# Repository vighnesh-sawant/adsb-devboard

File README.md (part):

# adsb-devboard
A devboard with an fpga  and an ADS-B reciever

# Why
When I was younger, I always wanted to tinker with radio stuff. When I learned airplanes broadcast  
all of their info on rf just like that, I tried naievly to process that using my phone thinking it had a rf reciever so it probably can.  
As it turns out it can't/ or is locked down so it can't.
So on learning about blueprint, I made by childhood dream come true!

# How
Get the pcb and a antenna(should be able to do for 1090Mhz),wire it to the correct gpio ports(more info soon)  
keep it in an open area, then flashing my firmware (not complete yet) should get you data about a good amount of flights in the vicinity    
(according to my research 50km ish)(more details once i try this out, I have done research but yk Murphy's law once I try out I'll have solid instructions!)

# Pics

# Bom
| JLCPCB BOM Tool - BOM Matching                                                      |                   |                             |                                          |               |                    |                        |                                                                                                                                                           |                 |                                                                                                                                                                                   |                                              |                                                                                                                                                                                                                              |                   |                                                                          |          |     |           |                 |
| ----------------------------------------------------------------------------------- | ----------------- | --------------------------- | ---------------------------------------- | ------------- | ------------------ | ---------------------- | --------------------------------------------------------------------------------------------------------------------------------------------------------- | --------------- | --------------------------------------------------------------------------------------------------------------------------------------------------------------------------------- | -------------------------------------------- | ---------------------------------------------------------------------------------------------------------------------------------------------------------------------------------------------------------------------------- | ----------------- | ------------------------------------------------------------------------ | -------- | --- | --------- | --------------- |
| BOM name：rev3_bom-JLCPCB Assembly Order.xlsx                                        |                   |                             | Download Time：2026-03-01 03:22:45        |               |                    |                        | * Our matching results are updated in real-time, but stock and prices may change. 
If it's been over 24 hours, please re-match before placing your order. |                 |                                                                                                                                                                                   |                                              |                                                                                                                                                                                                                              |                   |                                                                          |          |     |           |                 |
| PCB Assembled Qty：5                                                                 |                   |                             | Est. Total Price：59.8411                 |               |                    |                        |                                                                                                                                                           |                 |                                                                                                                                                                                   |                                              |                                                                                                                                                                                                                              |                   |                                                                          |          |     |           |                 |
| Your BOM                                                                            |                   |                             |                                          |               | Matched Parts      |                        |                                                                                                                                                           |                 |                                                                                                                                                                                   |                                              |                                                                                                                                                                                                                              | Order Information |                                                                          |          |     |           |                 |
| Top Designator                                                                      | Bottom Designator | Comment                     | Footprint                                | JLCPCB Part # | Matches            | Part #                 | Manufacturer                                                                                                                                              | Footprint       | Description                                                                                                                                                                       | Category                                     | Warning                                                                                                                                                                                                                      | JLCPCB Part #     | Product link                                                             | Lib Type | Qty | Source    | Total Price ($) |
| C1,C2                                                                               |                   | 33p                         | 0402                                     |               | Unconfirmed        | 0402CG330J500NT        | FH (Guangdong Fenghua Advanced Tech)                                                                                                                      | 0402            | 33pF 50V C0G ±5% 0402 Multilayer Ceramic Capacitors MLCC - SMD/SMT ROHS                                                                                                           | Multilayer Ceramic Capacitors MLCC - SMD/SMT | 1.The comment (0402CG330J500NT) of this part does not match the one (33p) provided in your BOM. Please confirm;                                                                                                              | C1562             | https://jlcpcb.com/partdetail/1914-0402CG330J500NT/C1562                 | Basic    | 4   | 4 JLCPCB  | 0.0048          |
| C10,C11,C12,C13,C14,C15,C17,C18,C19,C21,C33,C35,C37,C41,C43,C45,C47,C48,C6,C7,C8,C9 |                   | 100n                        | 0402                                     |               | Unconfirmed        | CL05B104KO5NNNC        | Samsung Electro-Mechanics                                                                                                                                 | 0402            | 100nF 16V X7R ±10% 0402 Multilayer Ceramic Capacitors MLCC - SMD/SMT ROHS                                                                                                         | Multilayer Ceramic Capacitors MLCC - SMD/SMT | 1.The comment (CL05B104KO5NNNC) of this part does not match the one (100n) provided in your BOM. Please confirm;                                                                                                             | C1525             | https://jlcpcb.com/partdetail/1877-CL05B104KO5NNNC/C1525                 | Basic    | 44  | 44 JLCPCB | 0.0572          |
| C16,C23,C3,C32,C34,C36,C38,C4,C40,C42,C44,C5                                        |                   | 4.7u                        | 0402                                     |               | Unconfirmed        | CL05A475MP5NRNC        | Samsung Electro-Mechanics                                                                                                                                 | 0402            | 10V 4.7uF X5R ±20% 0402 Multilayer Ceramic Capacitors MLCC - SMD/SMT ROHS                                                                                                         | Multilayer Ceramic Capacitors MLCC - SMD/SMT | 1.The comment (CL05A475MP5NRNC) of this part does not match the one (4.7u) provided in your BOM. Please confirm;                                                                                                             | C23733            | https://jlcpcb.com/partdetail/24469-CL05A475MP5NRNC/C23733               | Basic    | 24  | 24 JLCPCB | 0.12            |
| C20,C22                                                                             |                   | 22u                         | 0603                                     |               | Unconfirmed        | CL10A226MQ8NRNC        | Samsung Electro-Mechanics                                                                                                                                 | 0603            | 22uF 6.3V X5R ±20% 0603 Multilayer Ceramic Capacitors MLCC - SMD/SMT ROHS                                                                                                         | Multilayer Ceramic Capacitors MLCC - SMD/SMT | 1.The comment (CL10A226MQ8NRNC) of this part does not match the one (22u) provided in your BOM. Please confirm;                                                                                                              | C59461            | https://jlcpcb.com/partdetail/60514-CL10A226MQ8NRNC/C59461               | Basic    | 4   | 4 JLCPCB  | 0.038           |
| C24,C25                                                                             |                   | 10u                         | 0603                                     |               | Unconfirmed        | CL10A106KP8NNNC        | Samsung Electro-Mechanics                                                                                                                                 | 0603            | 10V 10uF X5R ±10% 0603 Multilayer Ceramic Capacitors MLCC - SMD/SMT ROHS                                                                                                          | Multilayer Ceramic Capacitors MLCC - SMD/SMT | 1.The comment (CL10A106KP8NNNC) of this part does not match the one (10u) provided in your BOM. Please confirm;                                                                                                              | C19702            | https://jlcpcb.com/partdetail/20411-CL10A106KP8NNNC/C19702               | Basic    | 4   | 4 JLCPCB  | 0.0264          |
| C26,C28                                                                             |                   | 680p                        | 0603                                     |               | Unconfirmed        | 0603B681K500NT         | FH (Guangdong Fenghua Advanced Tech)                                                                                                                      | 0603            | 50V 680pF X7R ±10% 0603 Multilayer Ceramic Capacitors MLCC - SMD/SMT ROHS                                                                                                         | Multilayer Ceramic Capacitors MLCC - SMD/SMT | 1.The comment (0603B681K500NT) of this part does not match the one (680p) provided in your BOM. Please confirm;                                                                                                              | C1630             | https://jlcpcb.com/partdetail/1982-0603B681K500NT/C1630                  | Extended | 20  | 20 JLCPCB | 0.064           |
| C29,C30                                                                             |                   | 100n                        | 0603                                     |               | Unconfirmed        | CC0603KRX7R9BB104      | YAGEO                                                                                                                                                     | 0603            | 100nF 50V X7R ±10% 0603 Multilayer Ceramic Capacitors MLCC - SMD/SMT ROHS                                                                                                         | Multilayer Ceramic Capacitors MLCC - SMD/SMT | 1.The comment (CC0603KRX7R9BB104) of this part does not match the one (100n) provided in your BOM. Please confirm;                                                                                                           | C14663            | https://jlcpcb.com/partdetail/YAGEO-CC0603KRX7R9BB104/C14663             | Basic    | 4   | 4 JLCPCB  | 0.01            |
| C31                                                                                 |                   | 1000p                       | 0402                                     |               | Unconfirmed        | 0402B102K500NT         | FH (Guangdong Fenghua Advanced Tech)                                                                                                                      | 0402            | 1nF 50V X7R ±10% 0402 Multilayer Ceramic Capacitors MLCC - SMD/SMT ROHS                                                                                                           | Multilayer Ceramic Capacitors MLCC - SMD/SMT | 1.The comment (0402B102K500NT) of this part does not match the one (1000p) provided in your BOM. Please confirm;                                                                                                             | C1523             | https://jlcpcb.com/partdetail/1875-0402B102K500NT/C1523                  | Basic    | 2   | 2 JLCPCB  | 0.0024          |
| C39                                                                                 |                   | 10u                         | 0402                                     |               | Unconfirmed        | CL05A106MQ5NUNC        | Samsung Electro-Mechanics                                                                                                                                 | 0402            | 10uF 6.3V X5R ±20% 0402 Multilayer Ceramic Capacitors MLCC - SMD/SMT ROHS                                                                                                         | Multilayer Ceramic Capacitors MLCC - SMD/SMT | 1.The comment (CL05A106MQ5NUNC) of this part does not match the one (10u) provided in your BOM. Please confirm;                                                                                                              | C15525            | https://jlcpcb.com/partdetail/16204-CL05A106MQ5NUNC/C15525               | Basic    | 2   | 2 JLCPCB  | 0.0112          |
| C46                                                                                 |                   | 1500p                       | 0603                                     |               | Select by Customer | 0603B152K500NT         | FH (Guangdong Fenghua Advanced Tech)                                                                                                                      | 0603            | 1.5nF 50V X7R ±10% 0603 Multilayer Ceramic Capacitors MLCC - SMD/SMT ROHS                                                                                                         | Multilayer Ceramic Capacitors MLCC - SMD/SMT | 1.The comment (0603B152K500NT) of this part does not match the one (1500p) provided in your BOM. Please confirm;
2.Multiple lines in the BOM have been matched to the same part. Please check if the matching is correct. ;  | C1595             | https://jlcpcb.com/partdetail/1947-0603B152K500NT/C1595                  | Extended | 20  | 20 JLCPCB | 0.058           |
| C52                                                                                 |                   | 1500pf                      | 0603                                     |               | Select by Customer | 0603B152K500NT         | FH (Guangdong Fenghua Advanced Tech)                                                                                                                      | 0603            | 1.5nF 50V X7R ±10% 0603 Multilayer Ceramic Capacitors MLCC - SMD/SMT ROHS                                                                                                         | Multilayer Ceramic Capacitors MLCC - SMD/SMT | 1.The comment (0603B152K500NT) of this part does not match the one (1500pf) provided in your BOM. Please confirm;
2.Multiple lines in the BOM have been matched to the same part. Please check if the matching is correct. ; | C1595             | https://jlcpcb.com/partdetail/1947-0603B152K500NT/C1595                  | Extended | 20  | 20 JLCPCB | 0.058           |
| C49                                                                                 |                   | 2.2u                        | 0603                                     |               | Unconfirmed        | CL10A225KO8NNNC        | Samsung Electro-Mechanics                                                                                                                                 | 0603            | 16V 2.2uF X5R ±10% 0603 Multilayer Ceramic Capacitors MLCC - SMD/SMT ROHS                                                                                                         | Multilayer Ceramic Capacitors MLCC - SMD/SMT | 1.The comment (CL10A225KO8NNNC) of this part does not match the one (2.2u) provided in your BOM. Please confirm;                                                                                                             | C23630            | https://jlcpcb.com/partdetail/24366-CL10A225KO8NNNC/C23630               | Basic    | 2   | 2 JLCPCB  | 0.0124          |
| C50                                                                                 |                   | 1000p                       | 0603                                     |               | Unconfirmed        | CL10B102KB8NNNC        | Samsung Electro-Mechanics                                                                                                                                 | 0603            | 1nF 50V X7R ±10% 0603 Multilayer Ceramic Capacitors MLCC - SMD/SMT ROHS                                                                                                           | Multilayer Ceramic Capacitors MLCC - SMD/SMT | 1.The comment (CL10B102KB8NNNC) of this part does not match the one (1000p) provided in your BOM. Please confirm;                                                                                                            | C1588             | https://jlcpcb.com/partdetail/1940-CL10B102KB8NNNC/C1588                 | Basic    | 2   | 2 JLCPCB  | 0.0066          |
| C53                                                                                 |                   | 3p                          | 0603                                     |               | Unconfirmed        | 0603CG3R0C500NT        | FH (Guangdong Fenghua Advanced Tech)                                                                                                                      | 0603            | 3pF 50V C0G 0603 Multilayer Ceramic Capacitors MLCC - SMD/SMT ROHS                                                                                                                | Multilayer Ceramic Capacitors MLCC - SMD/SMT | 1.The comment (0603CG3R0C500NT) of this part does not match the one (3p) provided in your BOM. Please confirm;                                                                                                               | C46219            | https://jlcpcb.com/partdetail/47222-0603CG3R0C500NT/C46219               | Extended | 20  | 20 JLCPCB | 0.062           |
| C54                                                                                 |                   | 200p                        | 0603                                     |               | Unconfirmed        | 0603B201K500NT         | FH (Guangdong Fenghua Advanced Tech)                                                                                                                      | 0603            | 200pF 50V X7R ±10% 0603 Multilayer Ceramic Capacitors MLCC - SMD/SMT ROHS                                                                                                         | Multilayer Ceramic Capacitors MLCC - SMD/SMT | 1.The comment (0603B201K500NT) of this part does not match the one (200p) provided in your BOM. Please confirm;                                                                                                              | C1600             | https://jlcpcb.com/partdetail/1952-0603B201K500NT/C1600                  | Extended | 20  | 20 JLCPCB | 0.088           |
| D1,D2,D3,D4,D5,D6                                                                   |                   | LED                         | 0603                                     |               | Unconfirmed        | KT-0603W               | Hubei KENTO Elec                                                                                                                                          | 0603            | 100mW 120° 2.6V~3.1V 360mcd 5mA Discrete Diode Top-mount White Yellow Lens 0603 LED Indication - Discrete ROHS                                                                    | LED Indication - Discrete                    | 1.The comment (KT-0603W) of this part does not match the one (LED) provided in your BOM. Please confirm;                                                                                                                     | C2290             | https://jlcpcb.com/partdetail/Hubei_KENTOElec-KT0603W/C2290              | Basic    | 12  | 12 JLCPCB | 0.1416          |
| FB1,FB2,FB3                                                                         |                   | FerriteBead                 | 0603                                     |               | Select by Customer | GZ1608D601TF           | Sunlord                                                                                                                                                   | 0603            | -55℃~+125℃ 1 200mA 450mΩ 600Ω@100MHz ±25% 0603 Ferrite Beads ROHS                                                                                                                 | Ferrite Beads                                |                                                                                                                                                                                                                              | C1002             | https://jlcpcb.com/partdetail/Sunlord-GZ1608D601TF/C1002                 | Basic    | 6   | 6 JLCPCB  | 0.0792          |
| J1                                                                                  |                   | USB_C_Receptacle_USB2.0_16P | USB_C_Receptacle_XKB_U262-16XN-4BVC11    |               | Select by Customer | TYPE-C 16PIN 2MD(073)  | SHOU HAN                                                                                                                                                  | SMD             | -25℃~+85℃ 1 16P 3A 5,000 times 5V Black Female Surface Mount, Right Angle Type-C SMD USB Connectors ROHS                                                                          | USB Connectors                               |                                                                                                                                                                                                                              | C2765186          | https://jlcpcb.com/partdetail/SHOUHAN-TYPE_C_16PIN_2MD_073/C2765186      | Extended | 3   | 3 JLCPCB  | 0.1953          |
| L1,L2,L3                                                                            |                   | AOTA-B201610S3R3-101-T      | IND-SMD_L2.0-W1.6_AOTA-B201610S3R3-101-T |               | Select by System   | AOTA-B201610S3R3-101-T | Abracon LLC                                                                                                                                               | 0806            | 0806 Power Inductors ROHS                                                                                                                                                         | Power Inductors                              |                                                                                                                                                                                                                              | C42411119         | https://jlcpcb.com/partdetail/AbraconLLC-AOTA_B201610S3R3_101T/C42411119 | Extended | 6   | 6 JLCPCB  | 1.7286          |
| L4,L5                                                                               |                   | HP0603-R10H-N               | IND-SMD_L1.6-W1.0                        |               | Select by System   | HP0603-R10H-N          | Chilisin Elec                                                                                                                                             | SMD,1.6x1mm     | 1.7GHz 100nH 470mA 49@150MHz 540mΩ Wire-wound chip inductor ±3% SMD,1.6x1mm Inductors (SMD) ROHS                                                                                  | Inductors (SMD)                              |                                                                                                                                                                                                                              | C2903685          | https://jlcpcb.com/partdetail/ChilisinElec-HP0603_R10HN/C2903685         | Extended | 6   | 6 JLCPCB  | 0.5478          |
| R1,R2                                                                               |                   | 5.1k                        | 0402                                     |               | Unconfirmed        | 0402WGF5101TCE         | UNI-ROYAL(Uniroyal Elec)                                                                                                                                  | 0402            | -55℃~+155℃ 5.1kΩ 50V 62.5mW Thick Film Resistor ±1% ±100ppm/℃ 0402 Chip Resistor - Surface Mount ROHS                                                                             | Chip Resistor - Surface Mount                | 1.The comment (0402WGF5101TCE) of this part does not match the one (5.1k) provided in your BOM. Please confirm;                                                                                                              | C25905            | https://jlcpcb.com/partdetail/26648-0402WGF5101TCE/C25905                | Basic    | 4   | 4 JLCPCB  | 0.0032          |
| R3,R4                                                                               |                   | 27                          | 0402                                     |               | Unconfirmed        | 0402WGF270JTCE         | UNI-ROYAL(Uniroyal Elec)                                                                                                                                  | 0402            | -55℃~+155℃ 27Ω 50V 62.5mW Thick Film Resistor ±1% ±100ppm/℃ 0402 Chip Resistor - Surface Mount ROHS                                                                               | Chip Resistor - Surface Mount                | 1.The comment (0402WGF270JTCE) of this part does not match the one (27) provided in your BOM. Please confirm;                                                                                                                | C25100            | https://jlcpcb.com/partdetail/25843-0402WGF270JTCE/C25100                | Extended | 20  | 20 JLCPCB | 0.016           |
| R6                                                                                  |                   | 33                          | 0402                                     |               | Unconfirmed        | 0402WGF330JTCE         | UNI-ROYAL(Uniroyal Elec)                                                                                                                                  | 0402            | -55℃~+155℃ 33Ω 50V 62.5mW Thick Film Resistor ±1% ±100ppm/℃ 0402 Chip Resistor - Surface Mount ROHS                                                                               | Chip Resistor - Surface Mount                | 1.The comment (0402WGF330JTCE) of this part does not match the one (33) provided in your BOM. Please confirm;                                                                                                                | C25105            | https://jlcpcb.com/partdetail/25848-0402WGF330JTCE/C25105                | Basic    | 2   | 2 JLCPCB  | 0.0016          |
| R10,R9                                                                              |                   | 51k                         | 0402                                     |               | Unconfirmed        | 0402WGF5102TCE         | UNI-ROYAL(Uniroyal Elec)                                                                                                                                  | 0402            | -55℃~+155℃ 50V 51kΩ 62.5mW Thick Film Resistor ±1% ±100ppm/℃ 0402 Chip Resistor - Surface Mount ROHS                                                                              | Chip Resistor - Surface Mount                | 1.The comment (0402WGF5102TCE) of this part does not match the one (51k) provided in your BOM. Please confirm;                                                                                                               | C25794            | https://jlcpcb.com/partdetail/26537-0402WGF5102TCE/C25794                | Basic    | 4   | 4 JLCPCB  | 0.0036          |
| R11                                                                                 |                   | 22k                         | 0402                                     |               | Unconfirmed        | 0402WGF2202TCE         | UNI-ROYAL(Uniroyal Elec)                                                                                                                                  | 0402            | -55℃~+155℃ 22kΩ 50V 62.5mW Thick Film Resistor ±1% ±100ppm/℃ 0402 Chip Resistor - Surface Mount ROHS                                                                              | Chip Resistor - Surface Mount                | 1.The comment (0402WGF2202TCE) of this part does not match the one (22k) provided in your BOM. Please confirm;                                                                                                               | C25768            | https://jlcpcb.com/partdetail/26511-0402WGF2202TCE/C25768                | Basic    | 2   | 2 JLCPCB  | 0.0016          |
| R12,R32                                                                             |                   | 100k                        | 0402                                     |               | Unconfirmed        | 0402WGF1003TCE         | UNI-ROYAL(Uniroyal Elec)                                                                                                                                  | 0402            | -55℃~+155℃ 100kΩ 50V 62.5mW Thick Film Resistor ±1% ±100ppm/℃ 0402 Chip Resistor - Surface Mount ROHS                                                                             | Chip Resistor - Surface Mount                | 1.The comment (0402WGF1003TCE) of this part does not match the one (100k) provided in your BOM. Please confirm;                                                                                                              | C25741            | https://jlcpcb.com/partdetail/26484-0402WGF1003TCE/C25741                | Basic    | 4   | 4 JLCPCB  | 0.0032          |
| R13                                                                                 |                   | 120                         | 0402                                     |               | Unconfirmed        | 0402WGF1200TCE         | UNI-ROYAL(Uniroyal Elec)                                                                                                                                  | 0402            | -55℃~+155℃ 120Ω 50V 62.5mW Thick Film Resistor ±1% ±100ppm/℃ 0402 Chip Resistor - Surface Mount ROHS                                                                              | Chip Resistor - Surface Mount                | 1.The comment (0402WGF1200TCE) of this part does not match the one (120) provided in your BOM. Please confirm;                                                                                                               | C25079            | https://jlcpcb.com/partdetail/25822-0402WGF1200TCE/C25079                | Basic    | 2   | 2 JLCPCB  | 0.0014          |
| R14,R15,R16,R17,R18,R19,R20,R21,R24,R27,R28                                         |                   | 100                         | 0402                                     |               | Unconfirmed        | 0402WGF1000TCE         | UNI-ROYAL(Uniroyal Elec)                                                                                                                                  | 0402            | -55℃~+155℃ 100Ω 50V 62.5mW Thick Film Resistor ±1% ±100ppm/℃ 0402 Chip Resistor - Surface Mount ROHS                                                                              | Chip Resistor - Surface Mount                | 1.The comment (0402WGF1000TCE) of this part does not match the one (100) provided in your BOM. Please confirm;                                                                                                               | C25076            | https://jlcpcb.com/partdetail/25819-0402WGF1000TCE/C25076                | Basic    | 22  | 22 JLCPCB | 0.0154          |
| R22,R30,R5,R7                                                                       |                   | 1K                          | 0402                                     |               | Unconfirmed        | 0402WGF1001TCE         | UNI-ROYAL(Uniroyal Elec)                                                                                                                                  | 0402            | -55℃~+155℃ 1kΩ 50V 62.5mW Thick Film Resistor ±1% ±100ppm/℃ 0402 Chip Resistor - Surface Mount ROHS                                                                               | Chip Resistor - Surface Mount                | 1.The comment (0402WGF1001TCE) of this part does not match the one (1K) provided in your BOM. Please confirm;                                                                                                                | C11702            | https://jlcpcb.com/partdetail/12256-0402WGF1001TCE/C11702                | Basic    | 8   | 8 JLCPCB  | 0.0056          |
| R25,R31,R8                                                                          |                   | 10K                         | 0402                                     |               | Unconfirmed        | 0402WGF1002TCE         | UNI-ROYAL(Uniroyal Elec)                                                                                                                                  | 0402            | -55℃~+155℃ 10kΩ 50V 62.5mW Thick Film Resistor ±1% ±100ppm/℃ 0402 Chip Resistor - Surface Mount ROHS                                                                              | Chip Resistor - Surface Mount                | 1.The comment (0402WGF1002TCE) of this part does not match the one (10K) provided in your BOM. Please confirm;                                                                                                               | C25744            | https://jlcpcb.com/partdetail/26487-0402WGF1002TCE/C25744                | Basic    | 6   | 6 JLCPCB  | 0.0048          |
| R26                                                                                 |                   | 2.2K                        | 0402                                     |               | Unconfirmed        | 0402WGF2201TCE         | UNI-ROYAL(Uniroyal Elec)                                                                                                                                  | 0402            | -55℃~+155℃ 2.2kΩ 50V 62.5mW Thick Film Resistor ±1% ±100ppm/℃ 0402 Chip Resistor - Surface Mount ROHS                                                                             | Chip Resistor - Surface Mount                | 1.The comment (0402WGF2201TCE) of this part does not match the one (2.2K) provided in your BOM. Please confirm;                                                                                                              | C25879            | https://jlcpcb.com/partdetail/26622-0402WGF2201TCE/C25879                | Basic    | 2   | 2 JLCPCB  | 0.0016          |
| R29                                                                                 |                   | 53.6                        | 0402                                     |               | Unconfirmed        | 0402WGF536JTCE         | UNI-ROYAL(Uniroyal Elec)                                                                                                                                  | 0402            | -55℃~+155℃ 50V 53.6Ω 62.5mW Thick Film Resistor ±1% ±100ppm/℃ 0402 Chip Resistor - Surface Mount ROHS                                                                             | Chip Resistor - Surface Mount                | 1.The comment (0402WGF536JTCE) of this part does not match the one (53.6) provided in your BOM. Please confirm;                                                                                                              | C423156           | https://jlcpcb.com/partdetail/416106-0402WGF536JTCE/C423156              | Extended | 20  | 20 JLCPCB | 0.014           |
| SW1                                                                                 |                   | SW_Push                     | SW-SMD_L3.9-W3.0-P4.45                   |               | Select by Customer | TS-1088-AR02016        | XUNPU                                                                                                                                                     | SMD,4x3mm       | -30℃~+80℃ 1.6N 100,000 cycles 12V 2mm 3mm 4mm 50mA Black Round Button SMD(SMT) Tab SPST Surface Mount,Vertical Without Bracket SMD,4x3mm Tactile Switches ROHS                    | Tactile Switches                             |                                                                                                                                                                                                                              | C720477           | https://jlcpcb.com/partdetail/XUNPU-TS_1088AR02016/C720477               | Basic    | 2   | 2 JLCPCB  | 0.096           |
| U1                                                                                  |                   | ICE40UP5K-SG48ITR           | QFN-48-1EP_7x7mm_P0.5mm_EP5.6x5.6mm      |               | Select by Customer | ICE40UP5K-SG48I        | Lattice                                                                                                                                                   | QFN-48-EP(7x7)  | -40℃~+100℃ 1171456bit 5280 660 QFN-48-EP(7x7) Programmable Logic Device (CPLDs/FPGAs) ROHS                                                                                        | Programmable Logic Device (CPLDs/FPGAs)      |                                                                                                                                                                                                                              | C2678152          | https://jlcpcb.com/partdetail/Lattice-ICE40UP5KSG48I/C2678152            | Extended | 2   | 2 JLCPCB  | 13.5164         |
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
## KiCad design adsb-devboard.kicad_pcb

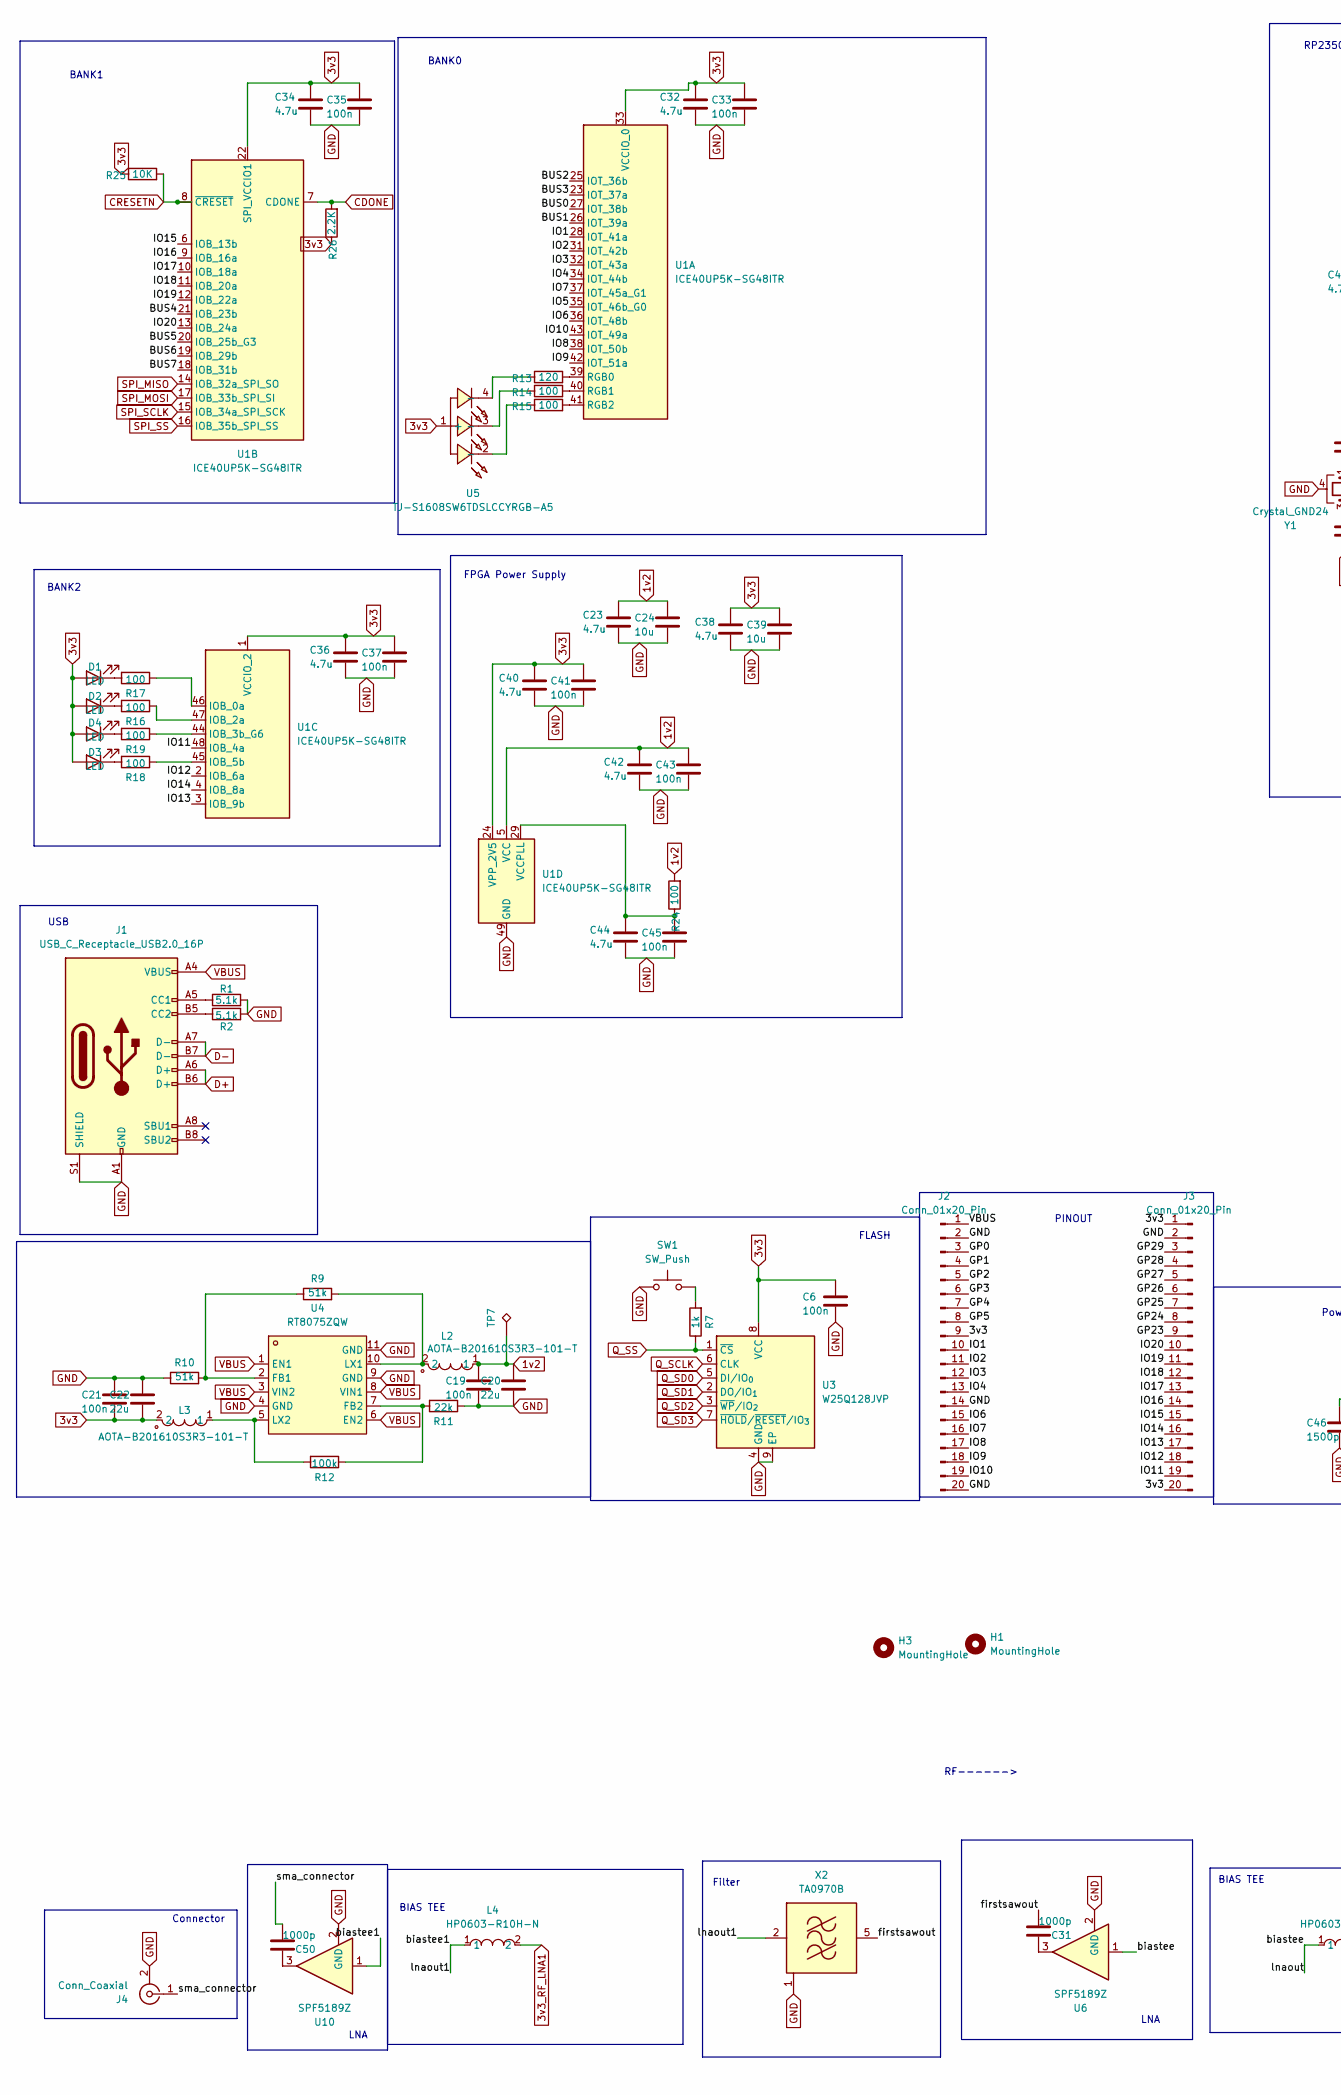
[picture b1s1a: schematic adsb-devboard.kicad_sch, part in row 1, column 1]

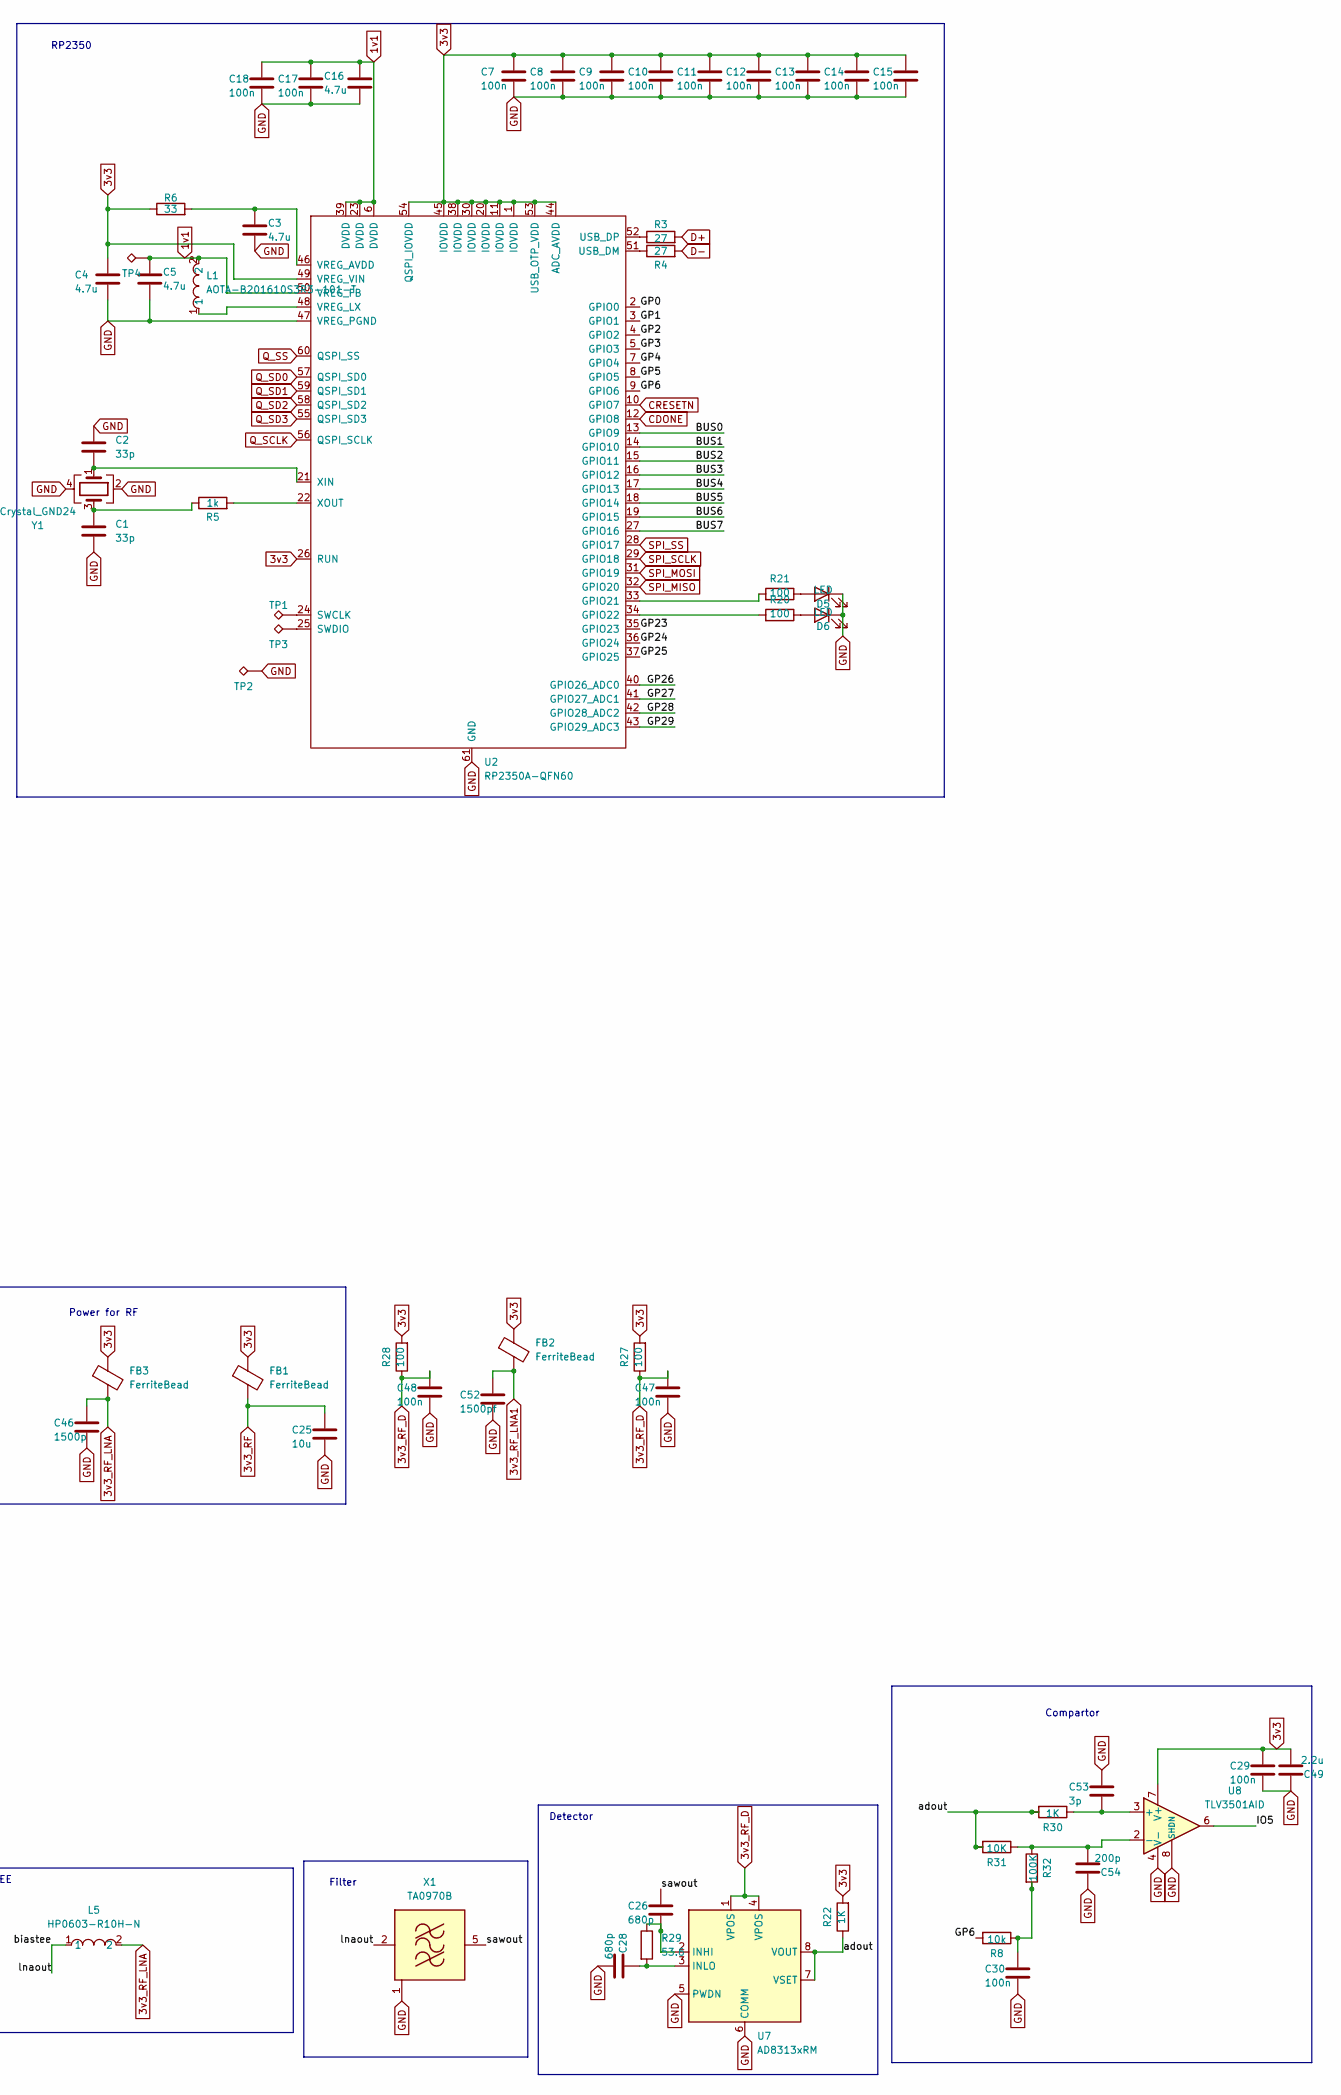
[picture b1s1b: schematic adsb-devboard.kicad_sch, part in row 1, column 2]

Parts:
C1, C2: 33p; C_0402_1005Metric
C3, C4, C5, C16, C23, C32, C34, C36, C38, C40, C42, C44: 4.7u; C_0402_1005Metric
C6, C7, C8, C9, C10, C11, C12, C13, C14, C15, C17, C18, C19, C21, C33, C35, C37, C41, C43, C45, C47, C48: 100n; C_0402_1005Metric
C20, C22: 22u; C_0603_1608Metric
C24, C25: 10u; C_0603_1608Metric
C26, C28: 680p; C_0603_1608Metric
C29, C30: 100n; C_0603_1608Metric
C31: 1000p; C_0402_1005Metric
C39: 10u; C_0402_1005Metric
C46: 1500p; C_0603_1608Metric
C49: 2.2u; C_0603_1608Metric
C50: 1000p; C_0603_1608Metric
C52: 1500pf; C_0603_1608Metric
C53: 3p; C_0603_1608Metric
C54: 200p; C_0603_1608Metric
D1, D2, D3, D4, D5, D6: LED; LED_0603_1608Metric
FB1, FB2, FB3: FerriteBead; L_0603_1608Metric
H1, H3: MountingHole; MountingHole_2.7mm_M2.5
J1: USB_C_Receptacle_USB2.0_16P; USB_C_Receptacle_XKB_U262-16XN-4BVC11
J2, J3: Conn_01x20_Pin; PinHeader_1x20_P2.54mm_Vertical
J4: Conn_Coaxial; SMA_BAT_Wireless_BWSMA-KWE-Z001
L1, L2, L3: AOTA-B201610S3R3-101-T; IND-SMD_L2.0-W1.6_AOTA-B201610S3R3-101-T; LCSC Part C42411119
L4, L5: HP0603-R10H-N; IND-SMD_L1.6-W1.0; LCSC Part C2903685
R1, R2: 5.1k; R_0402_1005Metric
R3, R4: 27; R_0402_1005Metric
R5, R7: 1k; R_0402_1005Metric
R6: 33; R_0402_1005Metric
R8: 10k; R_0402_1005Metric
R9, R10: 51k; R_0402_1005Metric
R11: 22k; R_0402_1005Metric
R12: 100k; R_0402_1005Metric
R13: 120; R_0402_1005Metric
R14, R15, R16, R17, R18, R19, R20, R21, R24, R27, R28: 100; R_0402_1005Metric
R22, R30: 1K; R_0402_1005Metric
R25, R31: 10K; R_0402_1005Metric
R26: 2.2K; R_0402_1005Metric
R29: 53.6; R_0402_1005Metric
R32: 100K; R_0402_1005Metric
SW1: SW_Push; SW-SMD_L3.9-W3.0-P4.45
TP1, TP2, TP3, TP4, TP7: TestPoint_Alt; TestPoint_Pad_D1.0mm
U1: ICE40UP5K-SG48ITR; QFN-48-1EP_7x7mm_P0.5mm_EP5.6x5.6mm
U2: RP2350A-QFN60; RP2350A_QFN-60_EP_7.75x7.75_Pitch0.4mm
U3: W25Q128JVP; WSON-8-1EP_6x5mm_P1.27mm_EP3.4x4.3mm
U4: RT8075ZQW; WDFN-10_L3.0-W3.0-P0.50-BL-EP; LCSC Part C250416
U5: TJ-S1608SW6TDSLCCYRGB-A5; LED-ARRAY-SMD_4P-L1.6-W0.8-BL-FD; LCSC Part C5356078
U6, U10: SPF5189Z; SOT-343-4_L2.0-W1.3-P1.30-LS2.1-BR
U7: AD8313xRM; MSOP-8_L3.0-W3.0-P0.65-LS4.9-BL
U8: TLV3501AID; SOP-8_L4.9-W3.9-P1.27-LS6.0-BL
X1, X2: TA0970B; FILTER-SMD_6P-L3.8-W3.8-P1.27-TL-3
Y1: Crystal_GND24; Crystal_SMD_3225-4Pin_3.2x2.5mm

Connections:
1v1: C5.1, C16.1, C17.1, C18.1, L1.2, TP4.1, U2.6 (DVDD), U2.23 (DVDD), U2.39 (DVDD), U2.50 (VREG_FB)
1v2: C19.1, C20.1, C23.1, C24.1, C42.1, C43.1, L2.1, R24.2, TP7.1, U1.5 (VCC), U1.30 (VCC)
3v3: C4.1, C6.1, C7.1, C8.1, C9.1, C10.1, C11.1, C12.1, C13.1, C14.1, C15.1, C21.2, C22.2, C29.1, C32.1, C33.1, C34.1, C35.1, C36.1, C37.1, C38.1, C39.1, C40.1, C41.1, C49.2, D1.2 (A), D2.2 (A), D3.2 (A), D4.2 (A), FB1.1, FB2.1, FB3.1, J2.9, J3.1, J3.20, L3.2, R6.1, R22.2, R25.1, R26.1, R27.2, R28.2, U1.1 (VCCIO_2), U1.22 (SPI_VCCIO1), U1.24 (VPP_2V5), U1.33 (VCCIO_0), U2.1 (IOVDD), U2.11 (IOVDD), U2.20 (IOVDD), U2.26 (RUN), U2.30 (IOVDD), U2.38 (IOVDD), U2.44 (ADC_AVDD), U2.45 (IOVDD), U2.49 (VREG_VIN), U2.53 (USB_OTP_VDD), U2.54 (QSPI_IOVDD), U3.8 (VCC), U5.1 (+), U8.7 (V+)
3v3_RF: C25.1, FB1.2
3v3_RF_D: C47.1, C48.1, R27.1, R28.1, U7.1 (VPOS), U7.4 (VPOS)
3v3_RF_LNA: C46.1, FB3.2, L5.2
3v3_RF_LNA1: C52.1, FB2.2, L4.2
/BUS0: U1.27 (IOT_38b), U2.13 (GPIO9)
/BUS1: U1.26 (IOT_39a), U2.14 (GPIO10)
/BUS2: U1.25 (IOT_36b), U2.15 (GPIO11)
/BUS3: U1.23 (IOT_37a), U2.16 (GPIO12)
/BUS4: U1.21 (IOB_23b), U2.17 (GPIO13)
/BUS5: U1.20 (IOB_25b_G3), U2.18 (GPIO14)
/BUS6: U1.19 (IOB_29b), U2.19 (GPIO15)
/BUS7: U1.18 (IOB_31b), U2.27 (GPIO16)
/GP0: J2.3, U2.2 (GPIO0)
/GP1: J2.4, U2.3 (GPIO1)
/GP2: J2.5, U2.4 (GPIO2)
/GP3: J2.6, U2.5 (GPIO3)
/GP4: J2.7, U2.7 (GPIO4)
/GP5: J2.8, U2.8 (GPIO5)
/GP6: R8.2, U2.9 (GPIO6)
/GP23: J3.9, U2.35 (GPIO23)
/GP24: J3.8, U2.36 (GPIO24)
/GP25: J3.7, U2.37 (GPIO25)
/GP26: J3.6, U2.40 (GPIO26_ADC0)
/GP27: J3.5, U2.41 (GPIO27_ADC1)
/GP28: J3.4, U2.42 (GPIO28_ADC2)
/GP29: J3.3, U2.43 (GPIO29_ADC3)
/IO1: J2.10, U1.28 (IOT_41a)
/IO2: J2.11, U1.31 (IOT_42b)
/IO3: J2.12, U1.32 (IOT_43a)
/IO4: J2.13, U1.34 (IOT_44b)
/IO5: U1.35 (IOT_46b_G0), U8.6
/IO6: J2.15, U1.36 (IOT_48b)
/IO7: J2.16, U1.37 (IOT_45a_G1)
/IO8: J2.17, U1.38 (IOT_50b)
/IO9: J2.18, U1.42 (IOT_51a)
/IO10: J2.19, U1.43 (IOT_49a)
/IO11: J3.19, U1.48 (IOB_4a)
/IO12: J3.18, U1.2 (IOB_6a)
/IO13: J3.17, U1.3 (IOB_9b)
/IO14: J3.16, U1.4 (IOB_8a)
/IO15: J3.15, U1.6 (IOB_13b)
/IO16: J3.14, U1.9 (IOB_16a)
/IO17: J3.13, U1.10 (IOB_18a)
/IO18: J3.12, U1.11 (IOB_20a)
/IO19: J3.11, U1.12 (IOB_22a)
/IO20: J3.10, U1.13 (IOB_24a)
/adout: R22.1, R30.2, R31.2, U7.7 (VSET), U7.8 (VOUT)
/biastee: L5.1, U6.1, X1.2 (IN)
/biastee1: L4.1, U10.1, X2.2 (IN)
/firstsawout: C31.2, X2.5 (OUT)
/sawout: C26.1, X1.5 (OUT)
/sma_connector: C50.2, J4.1 (In)
CDONE: R26.2, U1.7 (CDONE), U2.12 (GPIO8)
CRESETN: R25.2, U1.8 (~CRESET), U2.10 (GPIO7)
D+: J1.A6 (D+), J1.B6 (D+), R3.2
D-: J1.A7 (D-), J1.B7 (D-), R4.2
GND: C1.2, C2.1, C3.2, C4.2, C5.2, C6.2, C7.2, C8.2, C9.2, C10.2, C11.2, C12.2, C13.2, C14.2, C15.2, C16.2, C17.2, C18.2, C19.2, C20.2, C21.1, C22.1, C23.2, C24.2, C25.2, C28.2, C29.2, C30.2, C32.2, C33.2, C34.2, C35.2, C36.2, C37.2, C38.2, C39.2, C40.2, C41.2, C42.2, C43.2, C44.2, C45.2, C46.2, C47.2, C48.2, C49.1, C52.2, C53.1, C54.1, D5.1 (K), D6.1 (K), J1.A1 (GND), J1.A12 (GND), J1.B1 (GND), J1.B12 (GND), J1.S1 (SHIELD), J2.2, J2.14, J2.20, J3.2, J4.2 (Ext), R1.2, R2.2, R10.1, R11.1, SW1.1, TP2.1, U1.49 (GND), U2.47 (VREG_PGND), U2.61 (GND), U3.4 (GND), U3.9 (EP), U4.4 (GND), U4.9 (GND), U4.11 (GND), U6.2 (GND), U7.5 (PWDN), U7.6 (COMM), U8.4 (V-), U8.8 (SHDN), U10.2 (GND), X1.1 (GND), X1.3 (GND), X1.4 (GND), X1.6 (GND), X2.1 (GND), X2.3 (GND), X2.4 (GND), X2.6 (GND), Y1.2, Y1.4
unnamed: C1.1, R5.1, Y1.3
unnamed: C30.1, R8.1, R32.2
unnamed: C31.1, U6.3
unnamed: C50.1, U10.3
unnamed: D1.1 (K), R17.2
unnamed: D2.1 (K), R16.2
unnamed: D3.1 (K), R18.2
unnamed: D4.1 (K), R19.2
unnamed: D5.2 (A), R21.1
unnamed: D6.2 (A), R20.1
unnamed: J1.A5 (CC1), R1.1
unnamed: J1.B5 (CC2), R2.1
unnamed: R7.2, SW1.2
unnamed: R13.1, U5.4 (-)
unnamed: R14.1, U5.3 (-)
unnamed: R15.1, U5.2 (-)
unnamed: R13.2, U1.39 (RGB0)
unnamed: R14.2, U1.40 (RGB1)
unnamed: R15.2, U1.41 (RGB2)
unnamed: R17.1, U1.46 (IOB_0a)
unnamed: R16.1, U1.47 (IOB_2a)
unnamed: R19.1, U1.44 (IOB_3b_G6)
unnamed: R18.1, U1.45 (IOB_5b)
unnamed: C44.1, C45.1, R24.1, U1.29 (VCCPLL)
unnamed: R21.2, U2.33 (GPIO21)
unnamed: R20.2, U2.34 (GPIO22)
unnamed: TP1.1, U2.24 (SWCLK)
unnamed: TP3.1, U2.25 (SWDIO)
unnamed: R4.1, U2.51 (USB_DM)
unnamed: R3.1, U2.52 (USB_DP)
unnamed: C3.1, R6.2, U2.46 (VREG_AVDD)
unnamed: L1.1, U2.48 (VREG_LX)
unnamed: C2.2, U2.21 (XIN), Y1.1
unnamed: R5.2, U2.22 (XOUT)
unnamed: R9.1, R10.2, U4.2 (FB1)
unnamed: R11.2, R12.1, U4.7 (FB2)
unnamed: L2.2, R9.2, U4.10 (LX1)
unnamed: L3.1, R12.2, U4.5 (LX2)
unnamed: C26.2, R29.1, U7.2 (INHI)
unnamed: C28.1, R29.2, U7.3 (INLO)
unnamed: C53.2, R30.1, U8.3 (+)
unnamed: C54.2, R31.1, R32.1, U8.2 (-)
Q_SCLK: U2.56 (QSPI_SCLK), U3.6 (CLK)
Q_SD0: U2.57 (QSPI_SD0), U3.5 (DI/IO_{0})
Q_SD1: U2.59 (QSPI_SD1), U3.2 (DO/IO_{1})
Q_SD2: U2.58 (QSPI_SD2), U3.3 (~WP/IO_{2})
Q_SD3: U2.55 (QSPI_SD3), U3.7 (~HOLD/~RESET/IO_{3})
Q_SS: R7.1, U2.60 (QSPI_SS), U3.1 (~CS)
SPI_MISO: U1.14 (IOB_32a_SPI_SO), U2.32 (GPIO20)
SPI_MOSI: U1.17 (IOB_33b_SPI_SI), U2.31 (GPIO19)
SPI_SCLK: U1.15 (IOB_34a_SPI_SCK), U2.29 (GPIO18)
SPI_SS: U1.16 (IOB_35b_SPI_SS), U2.28 (GPIO17)
VBUS: J1.A4 (VBUS), J1.A9 (VBUS), J1.B4 (VBUS), J1.B9 (VBUS), J2.1, U4.1 (EN1), U4.3 (VIN2), U4.6 (EN2), U4.8 (VIN1)

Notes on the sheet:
BIAS TEE
LNA
Filter
BANK0
Power for RF
Connector
FLASH
BANK2
RP2350
PINOUT
BANK1
RF------>
Compartor
FPGA Power Supply
USB
Detector

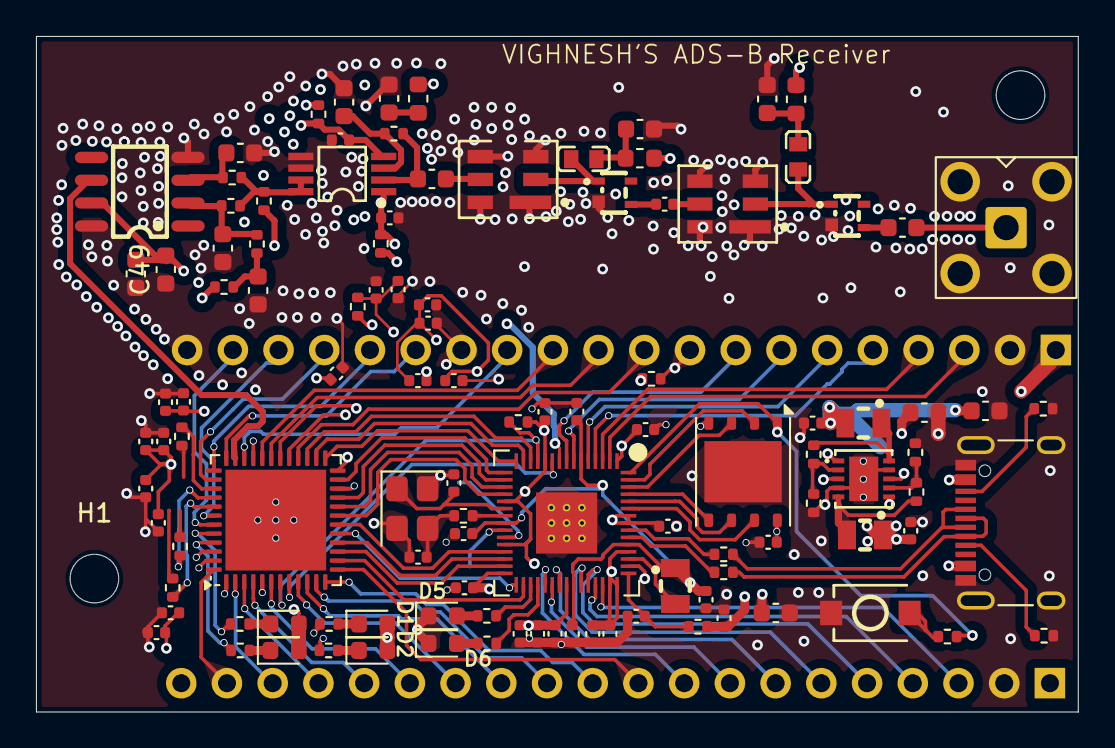
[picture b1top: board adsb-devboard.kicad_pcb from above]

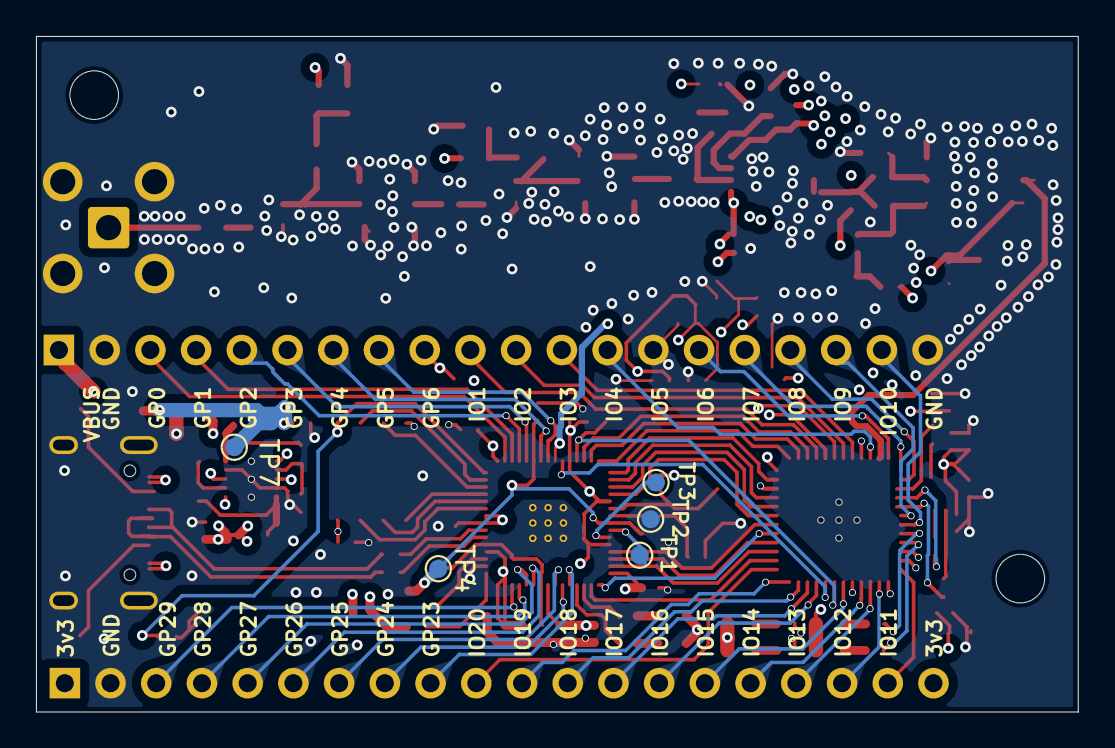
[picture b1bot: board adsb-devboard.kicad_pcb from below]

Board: 4 copper layers, 57.9 x 37.5 mm, 120 parts (7 on the bottom side), 110 nets.

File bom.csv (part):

JLCPCB BOM Tool - BOM Matching,,,,,,,,,,,,,,,,,
BOM name：rev1_bom-JLCPCB Assembly Order.xlsx,,,Download Time：2026-02-06 17:06:12,,,,"* Our matching results are updated in real-time, but stock and prices may change. 
If it's been over 24 hours, please re-match before placing your order.",,,,,,,,,,
PCB Assembled Qty：5,,,Est. Total Price：48.3408,,,,,,,,,,,,,,
Your BOM,,,,,Matched Parts,,,,,,,Order Information,,,,,
Top Designator,Bottom Designator,Comment,Footprint,JLCPCB Part #,Matches,Part # ,Manufacturer,Footprint,Description,Category,Warning,JLCPCB Part #,Product link,Lib Type,Qty,Source,Total Price ($)
"C1,C2",,33p,0402,,Unconfirmed,0402CG330J500NT,FH (Guangdong Fenghua Advanced Tech),0402,33pF 50V C0G ±5% 0402 Multilayer Ceramic Capacitors MLCC - SMD/SMT ROHS,Multilayer Ceramic Capacitors MLCC - SMD/SMT,1.The comment (0402CG330J500NT) of this part does not match the one (33p) provided in your BOM. Please confirm;,C1562,https://jlcpcb.com/partdetail/1914-0402CG330J500NT/C1562,Basic,4,4 JLCPCB,0.0044
"C10,C11,C12,C13,C14,C15,C17,C18,C19,C21,C29,C6,C7,C8,C9",,100n,0402,,Unconfirmed,CL05B104KO5NNNC,Samsung Electro-Mechanics,0402,100nF 16V X7R ±10% 0402 Multilayer Ceramic Capacitors MLCC - SMD/SMT ROHS,Multilayer Ceramic Capacitors MLCC - SMD/SMT,1.The comment (CL05B104KO5NNNC) of this part does not match the one (100n) provided in your BOM. Please confirm;,C1525,https://jlcpcb.com/partdetail/1877-CL05B104KO5NNNC/C1525,Basic,30,30 JLCPCB,0.039
"C16,C23,C3,C4,C5",,4.7u,0402,,Unconfirmed,CL05A475MP5NRNC,Samsung Electro-Mechanics,0402,10V 4.7uF X5R ±20% 0402 Multilayer Ceramic Capacitors MLCC - SMD/SMT ROHS,Multilayer Ceramic Capacitors MLCC - SMD/SMT,1.The comment (CL05A475MP5NRNC) of this part does not match the one (4.7u) provided in your BOM. Please confirm;,C23733,https://jlcpcb.com/partdetail/24469-CL05A475MP5NRNC/C23733,Basic,10,10 JLCPCB,0.052
"C20,C22",,22u,0603,,Unconfirmed,CL10A226MQ8NRNC,Samsung Electro-Mechanics,0603,22uF 6.3V X5R ±20% 0603 Multilayer Ceramic Capacitors MLCC - SMD/SMT ROHS,Multilayer Ceramic Capacitors MLCC - SMD/SMT,1.The comment (CL10A226MQ8NRNC) of this part does not match the one (22u) provided in your BOM. Please confirm;,C59461,https://jlcpcb.com/partdetail/60514-CL10A226MQ8NRNC/C59461,Basic,4,4 JLCPCB,0.0376
"C24,C25",,10u,0603,,Unconfirmed,CL10A106KP8NNNC,Samsung Electro-Mechanics,0603,10V 10uF X5R ±10% 0603 Multilayer Ceramic Capacitors MLCC - SMD/SMT ROHS,Multilayer Ceramic Capacitors MLCC - SMD/SMT,1.The comment (CL10A106KP8NNNC) of this part does not match the one (10u) provided in your BOM. Please confirm;,C19702,https://jlcpcb.com/partdetail/20411-CL10A106KP8NNNC/C19702,Basic,4,4 JLCPCB,0.026
"C26,C27,C28,C31",,100p,0603,,Unconfirmed,CL10C101JB8NNNC,Samsung Electro-Mechanics,0603,100pF 50V C0G ±5% 0603 Multilayer Ceramic Capacitors MLCC - SMD/SMT ROHS,Multilayer Ceramic Capacitors MLCC - SMD/SMT,1.The comment (CL10C101JB8NNNC) of this part does not match the one (100p) provided in your BOM. Please confirm;,C14858,https://jlcpcb.com/partdetail/15530-CL10C101JB8NNNC/C14858,Basic,8,8 JLCPCB,0.0312
C30,,1u,0603,,Unconfirmed,CL10A105KB8NNNC,Samsung Electro-Mechanics,0603,1uF 50V X5R ±10% 0603 Multilayer Ceramic Capacitors MLCC - SMD/SMT ROHS,Multilayer Ceramic Capacitors MLCC - SMD/SMT,1.The comment (CL10A105KB8NNNC) of this part does not match the one (1u) provided in your BOM. Please confirm;,C15849,https://jlcpcb.com/partdetail/16531-CL10A105KB8NNNC/C15849,Basic,2,2 JLCPCB,0.0112
"D1,D2,D3,D4,D5,D6",,LED,0603,,Unconfirmed,KT-0603W,Hubei KENTO Elec,0603,100mW 120° 2.6V~3.1V 360mcd 5mA Discrete Diode Top-mount White Yellow Lens 0603 LED Indication - Discrete ROHS,LED Indication - Discrete,1.The comment (KT-0603W) of this part does not match the one (LED) provided in your BOM. Please confirm;,C2290,https://jlcpcb.com/partdetail/Hubei_KENTOElec-KT0603W/C2290,Basic,12,12 JLCPCB,0.1356
"FB1,FB2,FB3",,FerriteBead,0603,,Select by Customer,GZ1608D601TF,Sunlord,0603,-55℃~+125℃ 1 200mA 450mΩ 600Ω@100MHz ±25% 0603 Ferrite Beads ROHS,Ferrite Beads,,C1002,https://jlcpcb.com/partdetail/Sunlord-GZ1608D601TF/C1002,Basic,6,6 JLCPCB,0.0732
J1,,USB_C_Receptacle_USB2.0_16P,USB_C_Receptacle_XKB_U262-16XN-4BVC11,,Select by Customer,TYPE-C 16PIN 2MD(073),SHOU HAN,SMD,"-25℃~+85℃ 1 16P 3A 5,000 times 5V Black Female Surface Mount, Right Angle Type-C SMD USB Connectors ROHS",USB Connectors,,C2765186,https://jlcpcb.com/partdetail/SHOUHAN-TYPE_C_16PIN_2MD_073/C2765186,Extended,3,3 JLCPCB,0.1929
J4,,Conn_Coaxial,SMA_BAT_Wireless_BWSMA-KWE-Z001,,Select by Customer,BWSMA-KWE-Z001,BAT WIRELESS,插件,1 5.3mm 50Ω Board Side Elbow Inner Bore SMA Plugin Coaxial Connectors (RF) ROHS,Coaxial Connectors (RF),,C496551,https://jlcpcb.com/partdetail/BATWIRELESS-BWSMA_KWEZ001/C496551,Extended,0,0 JLCPCB,0
"L1,L2,L3",,AOTA-B201610S3R3-101-T,IND-SMD_L2.0-W1.6_AOTA-B201610S3R3-101-T,,Select by System,AOTA-B201610S3R3-101-T,Abracon LLC,0806,0806 Power Inductors ROHS,Power Inductors,,C42411119,https://jlcpcb.com/partdetail/AbraconLLC-AOTA_B201610S3R3_10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,Extended,6,6 JLCPCB,1.6374
L4,,470nH,0402,,Select by System,LSCNB1005EETR47MB,Taiyo Yuden,0402,1.2A 1.2A 140mΩ 470nH Multilayer inductor ±20% 0402 Inductors (SMD) ROHS,Inductors (SMD),,C5788770,https://jlcpcb.com/partdetail/TaiyoYuden-LSCNB1005EETR47MB/C5788770,Extended,5,5 JLCPCB,0.7215
"R1,R2",,5.1k,0402,,Unconfirmed,0402WGF5101TCE,UNI-ROYAL(Uniroyal Elec),0402,-55℃~+155℃ 5.1kΩ 50V 62.5mW Thick Film Resistor ±1% ±100ppm/℃ 0402 Chip Resistor - Surface Mount ROHS,Chip Resistor - Surface Mount,1.The comment (0402WGF5101TCE) of this part does not match the one (5.1k) provided in your BOM. Please confirm;,C25905,https://jlcpcb.com/partdetail/26648-0402WGF5101TCE/C25905,Basic,4,4 JLCPCB,0.0032
"R3,R4",,27,0402,,Select by Customer,0402WGF220JTCE,UNI-ROYAL(Uniroyal Elec),0402,-55℃~+155℃ 22Ω 50V 62.5mW Thick Film Resistor ±1% ±100ppm/℃ 0402 Chip Resistor - Surface Mount ROHS,Chip Resistor - Surface Mount,1.The comment (0402WGF220JTCE) of this part does not match the one (27) provided in your BOM. Please confirm;,C25092,https://jlcpcb.com/partdetail/25835-0402WGF220JTCE/C25092,Basic,4,4 JLCPCB,0.0032
"R5,R7",,1k,0402,,Unconfirmed,0402WGF1001TCE,UNI-ROYAL(Uniroyal Elec),0402,-55℃~+155℃ 1kΩ 50V 62.5mW Thick Film Resistor ±1% ±100ppm/℃ 0402 Chip Resistor - Surface Mount ROHS,Chip Resistor - Surface Mount,1.The comment (0402WGF1001TCE) of this part does not match the one (1k) provided in your BOM. Please confirm;,C11702,https://jlcpcb.com/partdetail/12256-0402WGF1001TCE/C11702,Basic,4,4 JLCPCB,0.0028
R6,,33,0402,,Unconfirmed,0402WGF330JTCE,UNI-ROYAL(Uniroyal Elec),0402,-55℃~+155℃ 33Ω 50V 62.5mW Thick Film Resistor ±1% ±100ppm/℃ 0402 Chip Resistor - Surface Mount ROHS,Chip Resistor - Surface Mount,1.The comment (0402WGF330JTCE) of this part does not match the one (33) provided in your BOM. Please confirm;,C25105,https://jlcpcb.com/partdetail/25848-0402WGF330JTCE/C25105,Basic,2,2 JLCPCB,0.0016
R8,,10k,0402,,Unconfirmed,0402WGF1002TCE,UNI-ROYAL(Uniroyal Elec),0402,-55℃~+155℃ 10kΩ 50V 62.5mW Thick Film Resistor ±1% ±100ppm/℃ 0402 Chip Resistor - Surface Mount ROHS,Chip Resistor - Surface Mount,1.The comment (0402WGF1002TCE) of this part does not match the one (10k) provided in your BOM. Please confirm;,C25744,https://jlcpcb.com/partdetail/26487-0402WGF1002TCE/C25744,Basic,2,2 JLCPCB,0.0016
"R10,R9",,51k,0402,,Unconfirmed,0402WGF5102TCE,UNI-ROYAL(Uniroyal Elec),0402,-55℃~+155℃ 50V 51kΩ 62.5mW Thick Film Resistor ±1% ±100ppm/℃ 0402 Chip Resistor - Surface Mount ROHS,Chip Resistor - Surface Mount,1.The comment (0402WGF5102TCE) of this part does not match the one (51k) provided in your BOM. Please confirm;,C25794,https://jlcpcb.com/partdetail/26537-0402WGF5102TCE/C25794,Basic,4,4 JLCPCB,0.0036
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
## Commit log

2026-02-03 Add all stuff
2026-02-03 add bom
2026-02-06 everything seems ready
2026-02-06 basic firmware will work on this soon
2026-02-12 add lcsc.csv
2026-02-18 Revise setup instructions in README
    Updated instructions for setting up the PCB and antenna.
2026-02-24 sch cleanup and little upgrade
2026-02-24 rerouted rf
2026-02-24 rerouted rf2
2026-02-25 upddateeedd schematic
2026-02-25 reeeerrouuuteed
2026-02-28 I HAVE ROUTED THIS FOR THE NTH TIME IDK I HAVE LOST COUNT
2026-02-28 admin stuff
